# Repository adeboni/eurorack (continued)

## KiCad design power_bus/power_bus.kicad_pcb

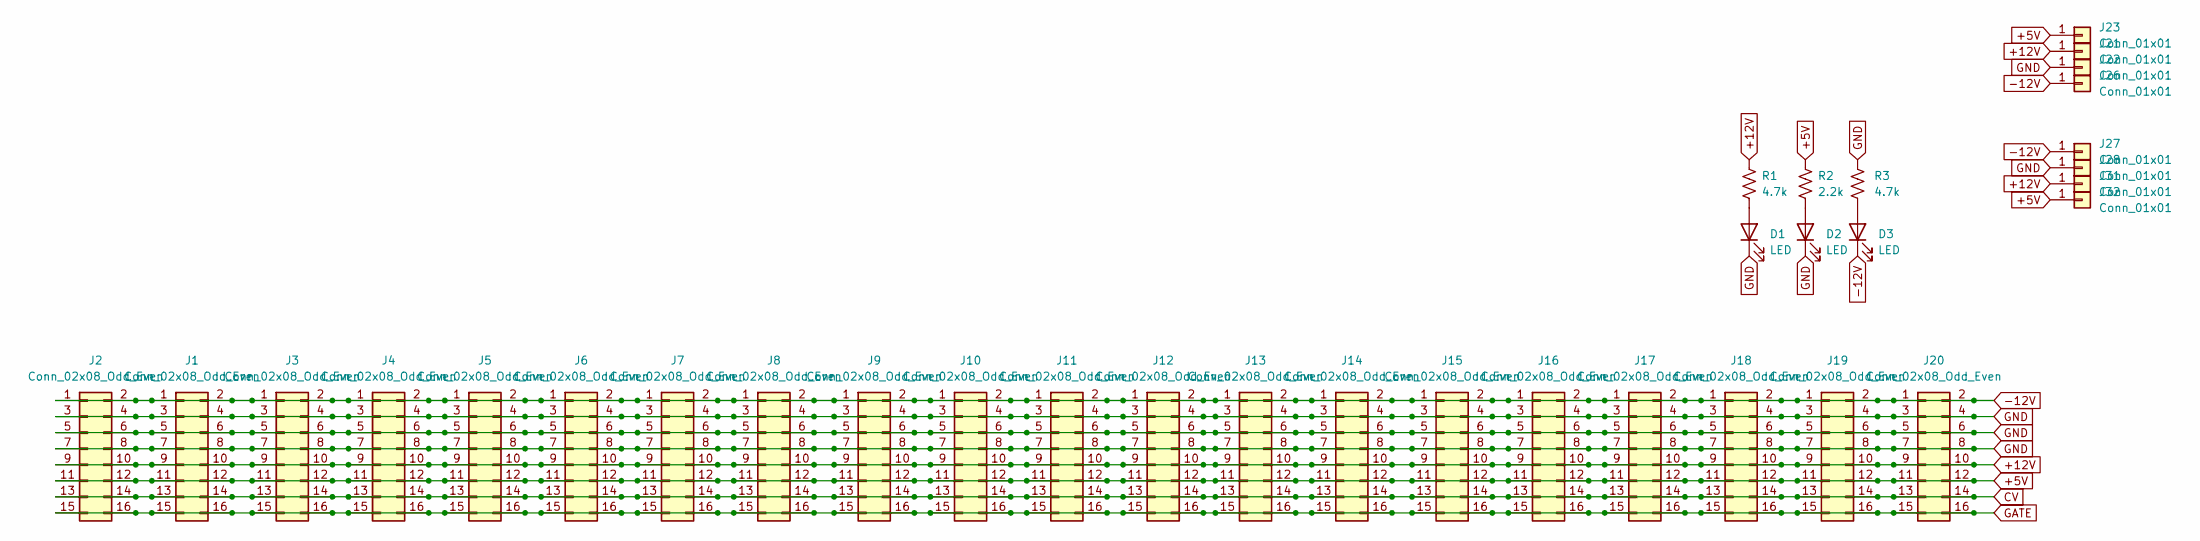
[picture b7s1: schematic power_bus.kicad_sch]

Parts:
D1, D2, D3: LED; LED_D3.0mm
J1, J2, J3, J4, J5, J6, J7, J8, J9, J10, J11, J12, J13, J14, J15, J16, J17, J18, J19, J20: Conn_02x08_Odd_Even; IDC-Header_2x08_P2.54mm_Vertical
J21, J22, J23, J26, J27, J28, J31, J32: Conn_01x01; SPADE
R1, R3: 4.7k; R_Axial_DIN0207_L6.3mm_D2.5mm_P7.62mm_Horizontal
R2: 2.2k; R_Axial_DIN0207_L6.3mm_D2.5mm_P7.62mm_Horizontal

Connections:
+5V: J1.11, J1.12, J2.11, J2.12, J3.11, J3.12, J4.11, J4.12, J5.11, J5.12, J6.11, J6.12, J7.11, J7.12, J8.11, J8.12, J9.11, J9.12, J10.11, J10.12, J11.11, J11.12, J12.11, J12.12, J13.11, J13.12, J14.11, J14.12, J15.11, J15.12, J16.11, J16.12, J17.11, J17.12, J18.11, J18.12, J19.11, J19.12, J20.11, J20.12, J23.1, J32.1, R2.1
+12V: J1.9, J1.10, J2.9, J2.10, J3.9, J3.10, J4.9, J4.10, J5.9, J5.10, J6.9, J6.10, J7.9, J7.10, J8.9, J8.10, J9.9, J9.10, J10.9, J10.10, J11.9, J11.10, J12.9, J12.10, J13.9, J13.10, J14.9, J14.10, J15.9, J15.10, J16.9, J16.10, J17.9, J17.10, J18.9, J18.10, J19.9, J19.10, J20.9, J20.10, J21.1, J31.1, R1.1
-12V: D3.1 (K), J1.1, J1.2, J2.1, J2.2, J3.1, J3.2, J4.1, J4.2, J5.1, J5.2, J6.1, J6.2, J7.1, J7.2, J8.1, J8.2, J9.1, J9.2, J10.1, J10.2, J11.1, J11.2, J12.1, J12.2, J13.1, J13.2, J14.1, J14.2, J15.1, J15.2, J16.1, J16.2, J17.1, J17.2, J18.1, J18.2, J19.1, J19.2, J20.1, J20.2, J26.1, J27.1
CV: J1.13, J1.14, J2.13, J2.14, J3.13, J3.14, J4.13, J4.14, J5.13, J5.14, J6.13, J6.14, J7.13, J7.14, J8.13, J8.14, J9.13, J9.14, J10.13, J10.14, J11.13, J11.14, J12.13, J12.14, J13.13, J13.14, J14.13, J14.14, J15.13, J15.14, J16.13, J16.14, J17.13, J17.14, J18.13, J18.14, J19.13, J19.14, J20.13, J20.14
GATE: J1.15, J1.16, J2.15, J2.16, J3.15, J3.16, J4.15, J4.16, J5.15, J5.16, J6.15, J6.16, J7.15, J7.16, J8.15, J8.16, J9.15, J9.16, J10.15, J10.16, J11.15, J11.16, J12.15, J12.16, J13.15, J13.16, J14.15, J14.16, J15.15, J15.16, J16.15, J16.16, J17.15, J17.16, J18.15, J18.16, J19.15, J19.16, J20.15, J20.16
GND: D1.1 (K), D2.1 (K), J1.3, J1.4, J1.5, J1.6, J1.7, J1.8, J2.3, J2.4, J2.5, J2.6, J2.7, J2.8, J3.3, J3.4, J3.5, J3.6, J3.7, J3.8, J4.3, J4.4, J4.5, J4.6, J4.7, J4.8, J5.3, J5.4, J5.5, J5.6, J5.7, J5.8, J6.3, J6.4, J6.5, J6.6, J6.7, J6.8, J7.3, J7.4, J7.5, J7.6, J7.7, J7.8, J8.3, J8.4, J8.5, J8.6, J8.7, J8.8, J9.3, J9.4, J9.5, J9.6, J9.7, J9.8, J10.3, J10.4, J10.5, J10.6, J10.7, J10.8, J11.3, J11.4, J11.5, J11.6, J11.7, J11.8, J12.3, J12.4, J12.5, J12.6, J12.7, J12.8, J13.3, J13.4, J13.5, J13.6, J13.7, J13.8, J14.3, J14.4, J14.5, J14.6, J14.7, J14.8, J15.3, J15.4, J15.5, J15.6, J15.7, J15.8, J16.3, J16.4, J16.5, J16.6, J16.7, J16.8, J17.3, J17.4, J17.5, J17.6, J17.7, J17.8, J18.3, J18.4, J18.5, J18.6, J18.7, J18.8, J19.3, J19.4, J19.5, J19.6, J19.7, J19.8, J20.3, J20.4, J20.5, J20.6, J20.7, J20.8, J22.1, J28.1, R3.1
unnamed: D1.2 (A), R1.2
unnamed: D2.2 (A), R2.2
unnamed: D3.2 (A), R3.2

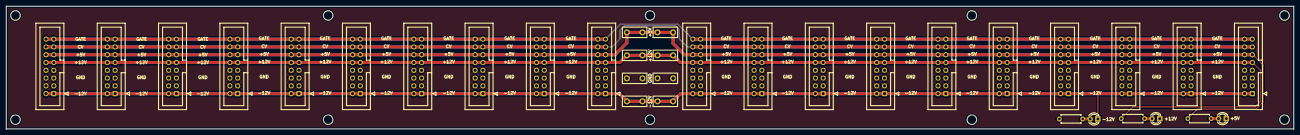
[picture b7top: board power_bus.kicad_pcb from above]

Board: 2 copper layers, 420.0 x 40.0 mm, 34 parts (0 on the bottom side), 9 nets.

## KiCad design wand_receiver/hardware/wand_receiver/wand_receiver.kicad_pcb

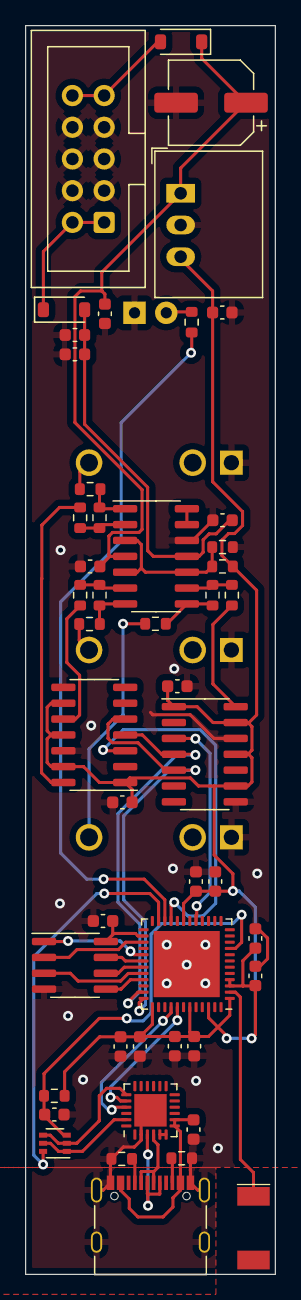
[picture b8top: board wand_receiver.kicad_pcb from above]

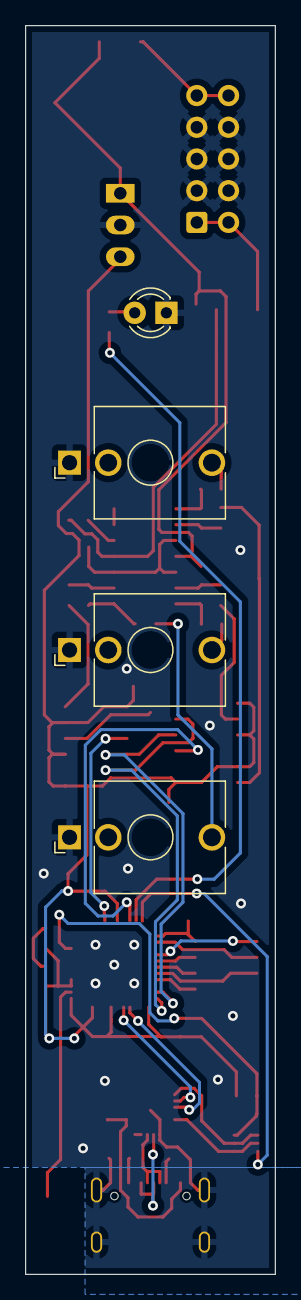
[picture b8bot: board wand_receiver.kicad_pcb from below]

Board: 2 copper layers, 20.0 x 100.0 mm, 52 parts (4 on the bottom side), 46 nets.

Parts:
AE1: Antenna_Chip; NN01-102
C1, C2, C3, C4, C7, C8, C9, C16: 10u; C_0603_1608Metric
C5: 100u; CP_Elec_6.3x5.4
C10, C11, C12, C13, C15, C17, C18, C19, C20, C21: 100n; C_0603_1608Metric
C14: 1u; C_0603_1608Metric
D1, D2: SM4007; D_SOD-123
D3: LED; LED_D3.0mm
J1, J3, J4: AudioJack2_SwitchT; Jack_3.5mm_QingPu_WQP-PJ398SM_Vertical_CircularHoles
J2: Conn_02x05_Odd_Even; IDC-Header_2x05_P2.54mm_Vertical
J5: USB_C_Receptacle_USB2.0; USB_C_Receptacle_Palconn_UTC16-G
Q2: MUN5214DW1T1G; SOT-363_SC-70-6
R1: 2k; R_0603_1608Metric
R2, R15: 1.2k; R_0603_1608Metric
R3, R6, R8, R9: 10k; R_0603_1608Metric
R4, R5, R7: 3.3k; R_0603_1608Metric
R10, R11: 5.1k; R_0603_1608Metric
R12, R13, R14: 220; R_0603_1608Metric
U1: R-783.3-1.0; Converter_DCDC_RECOM_R-78E-0.5_THT
U2, U3: MCP4922-ESL; SOIC-14_3.9x8.7mm_P1.27mm
U4: LM324; SOIC-14_3.9x8.7mm_P1.27mm
U5: LY68L6400SLIT; SOIC-8_3.9x4.9mm_P1.27mm
U6: ESP32-PICO-D4; QFN-48-1EP_7x7mm_P0.5mm_EP5.3x5.3mm
U8: CP2104; QFN-24-1EP_4x4mm_P0.5mm_EP2.6x2.6mm

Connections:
+3V3: C1.1, C2.1, C3.1, C4.1, C10.1, C11.1, C12.1, C13.1, C16.1, C17.2, C18.2, R1.2, R8.1, U1.3 (OUT), U2.1 (VDD), U2.9 (~SHDN), U2.11 (VrefB), U2.13 (VrefA), U3.1 (VDD), U3.9 (~SHDN), U3.11 (VrefB), U3.13 (VrefA), U6.1 (VDDA), U6.3 (VDDA3P3), U6.4 (VDDA3P3), U6.19 (VDD3P3_RTC), U6.37 (VDD3P3_CPU), U6.43 (VDDA), U6.46 (VDDA)
+12V: C5.1, C9.1, C20.2, D1.1 (K), U1.1 (IN), U4.4 (V+)
-12V: C7.2, C8.2, C21.1, D2.2 (A), U4.11 (V-)
CS_0: U2.3 (~CS), U6.21 (IO15)
CS_1: U3.3 (~CS), U6.17 (IO14)
DTR: Q2.1 (E2), Q2.5 (B1), U8.23 (~DTR)
GND: C1.2, C2.2, C3.2, C4.2, C5.2, C7.1, C8.1, C9.2, C10.2, C11.2, C12.2, C13.2, C14.2, C15.2, C16.2, C17.1, C18.1, C19.2, C20.1, C21.2, D3.1 (K), J1.S, J2.3, J2.4, J2.5, J2.6, J2.7, J2.8, J3.S, J4.S, J5.A1 (GND), J5.A12 (GND), J5.B1 (GND), J5.B12 (GND), J5.S1 (SHIELD), R2.1, R10.2, R11.2, U1.2 (GND), U2.8 (~LDAC), U2.12 (AVSS), U3.8 (~LDAC), U3.12 (AVSS), U4.12 (+), U5.4 (VSS), U6.49 (GND), U8.2 (GND), U8.25 (GND)
GPIO0: Q2.6 (C2), U6.23 (IO0)
GPIO2: R15.2, U6.22 (IO2)
GPIO7: U5.3 (SIO2), U6.32 (SD0)
GPIO8: U5.5 (SI/SIO), U6.33 (SD1)
GPIO10: U5.1 (~CE), U6.29 (SD3/IO10)
GPIO11: U5.7 (SIO3), U6.30 (CMD)
GPIO17: U5.2 (SO/SIO), U6.27 (IO17)
MOSI: U2.5 (SDI), U3.5 (SDI), U6.36 (IO23)
unnamed: AE1.1 (FEED), U6.2 (LNA_IN)
unnamed: D1.2 (A), J2.9, J2.10
unnamed: D2.1 (K), J2.1, J2.2
unnamed: D3.2 (A), R15.1
unnamed: J1.T, R12.2
unnamed: J3.T, R13.2
unnamed: J4.T, R14.2
unnamed: J5.A5 (CC1), R10.1
unnamed: J5.B5 (CC2), R11.1
unnamed: R3.2, R12.1, U4.1
unnamed: R6.2, R13.1, U4.7
unnamed: R9.2, R14.1, U4.8
unnamed: R3.1, R4.1, U4.2 (-)
unnamed: R5.1, R6.1, U4.6 (-)
unnamed: R7.1, R9.1, U4.9 (-)
unnamed: U4.13 (-), U4.14
unnamed: J5.A6 (D+), J5.B6 (D+), U8.3 (D+)
unnamed: J5.A7 (D-), J5.B7 (D-), U8.4 (D-)
unnamed: U8.5 (VIO), U8.6 (VDD)
PITCH: R5.2, U2.10 (VoutB)
RAM_CLK: U5.6 (SCLK), U6.31 (CLK)
RESET: C14.1, Q2.3 (C1), R8.2, U6.9 (EN)
ROLL: R7.2, U3.14 (VoutA)
RTS: Q2.2 (B2), Q2.4 (E1), U8.19 (~RTS)
RXD: U6.40 (U0RXD/IO3), U8.21 (TXD)
SCK: U2.4 (SCK), U3.4 (SCK), U6.35 (IO18)
TXD: U6.41 (U0TXD/IO1), U8.20 (RXD)
VBUS: C19.1, J5.A4 (VBUS), J5.A9 (VBUS), J5.B4 (VBUS), J5.B9 (VBUS), U8.7 (REGIN), U8.8 (VBUS)
VDDSDIO: C15.1, U5.8 (VCC), U6.26 (VDD_SDIO)
V_BIAS: R1.1, R2.2, U4.3 (+), U4.5 (+), U4.10 (+)
YAW: R4.2, U2.14 (VoutA)

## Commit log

2019-07-09 added front panels
2019-07-10 added code
2019-07-12 added fiber optics mounting bracket
2020-05-27 added csgo_gsi
2021-03-11 updated the geiger module
2022-02-18 added ecg and safety valve modules
2022-12-08 Create LICENSE
2022-12-08 Added new modules
2023-07-14 Added mindwave alternate firmware
2023-11-15 Updated filenames
2023-11-15 Added carbon mic and milkdrop projects
2024-02-13 Added noise toaster
2024-04-01 Created rev 2
2024-04-10 Fixed FFC connector footprint
2024-05-16 Added missing base resistor
2024-05-16 Added raspberry pi setup
2024-07-23 Added tx2 version of milkdrop
2024-08-14 Create power_bus
2024-08-16 Added mega_12v_pwr
2024-08-16 Updated gerbers
2024-08-19 Added fan connector
2024-08-19 Switched to PWM fan controller
2024-08-20 Added more ground terminals
2024-08-20 Fixed potentiometer polarities
2024-09-18 Updated resistor values
2024-09-24 Moved spade connectors
2024-09-26 Added spring expander
2024-09-27 Added laser controller
2024-10-01 Replaced 3.3V regulator
2024-10-02 Added wand receiver
2024-10-02 Added production files
2024-10-07 Added electrolytic caps
2024-11-26 Added mult
2024-11-27 Updated power bus
2024-12-03 Added keystep expander
2024-12-21 Added transformer
2025-02-07 Updated ga module production files
2025-02-28 Simplified schematic
2025-11-12 Added theremin project
2026-01-08 Updated trace widths and capacitor values
